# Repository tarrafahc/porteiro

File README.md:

porteiro
========

Repositório do porteiro do Tarrafa

O que é?
--------

O porteiro é o programa que roda no mula-sem-cabeça e serve principalmente para avisar quando tem ou não gente no Tarrafa. O porteiro centraliza várias funções. São elas: botão de presença, painel de LEDs, tomadas controladas por relé (pra ninguém esquecer a cafeteira ligada) e 'mood lamp'.

Estrutura dos arquivos
----------------------

A pasta 'arduino' tem o código que roda na plaquinha de arduino do porteiro. Este código atualiza o painel de LEDs com informação vinda pela serial, manda informação de alteração do estado do botão pela serial e controla a tomada e o 'mood lamp'.

A pasta 'eagle' tem os esquemáticos e o layout da plaquinha do shield de arduino do porteiro.

A pasta 'fonte' contém a fonte criada colaborativamente pelo Tarrafa para mostrar coisas no painel.

O script 'porteiro.py' roda no mula-sem-cabeça e fica mandando texto para o painel de LEDs e lendo informação do botão de presença.

Botão
-----

O botão deve ser pressionado pela primeira pessoa que entra no Tarrafa e pela última pessoa que sai do Tarrafa. Ao ligar, o botão manda uma mensagem para o mula-sem-cabeça para que ele atualize o status online do Tarrafa e acende a tomada controlada. Ao desligar, o botão manda novamente a mensagem para o mula-sem-cabeça e prepara a tomada para ser desligada.

Tomada controlada
-----------------

Na tomada controlada ficam ligadas (por enquanto) a luz externa do Tarrafa e a cafeteira. A tomada desliga um minuto depois de o botão ser desligado, dando tempo para que a luz externa ilumine a porta enquanto ela é fechada. A cafeteira também é desligada automaticamente para ninguém esquecer de desligá-la...

Painel de LEDs
--------------

O painel de LEDs foi reutilizado de alguma sucata. Durante encontros da N.E.R.D., foi feita a engenharia reversa do circuito eletrônico e foi feita uma interface para controlá-lo pelo Arduino. O painel tem 10 matrizes de 7x5 LEDs verdes/vermelhos. Dá pra passar qualquer coisa nos 10 caracteres do painel, mas no momento o que passa é a data, a hora e alguma mensagem de auto-ajuda qualquer...

Mood Lamp
---------

A 'mood lamp' fica ligada enquanto tem gente no Tarrafa. As cores da lâmpada ficam variando aleatoriamente num LED RGB.

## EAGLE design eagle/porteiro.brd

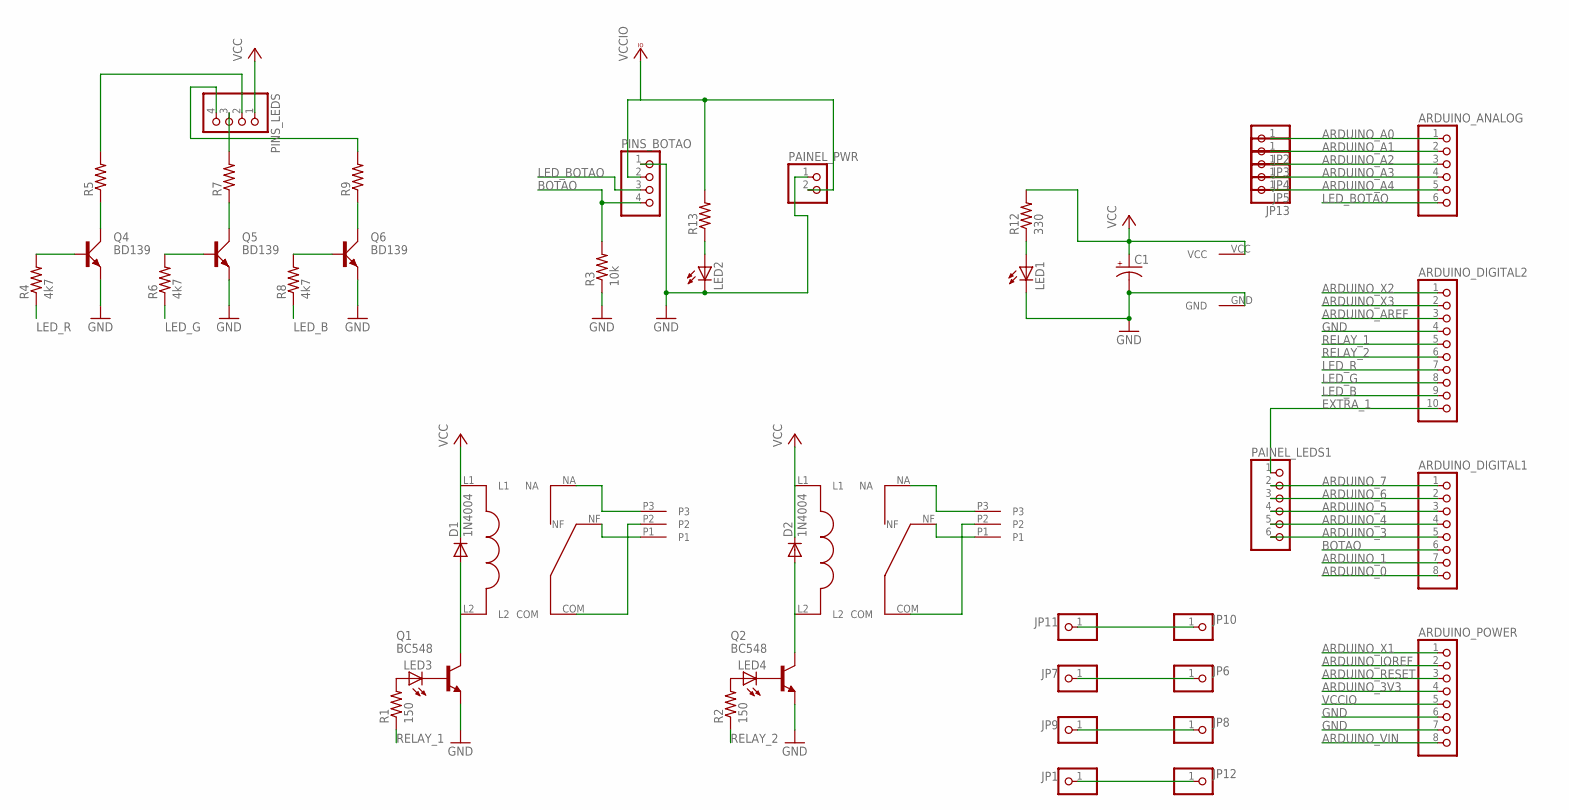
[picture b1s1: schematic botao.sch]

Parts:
ARDUINO_ANALOG: PINHD-1X6; 1X06
ARDUINO_DIGITAL1: PINHD-1X8; 1X08
ARDUINO_DIGITAL2: PINHD-1X10; 1X10
ARDUINO_POWER: PINHD-1X8; 1X08
C1: CPOL-USE5-10.5; E5-10,5
D1, D2: 1N4004; DO41-10
JP1, JP2, JP3, JP4, JP5, JP6, JP7, JP8, JP9, JP10, JP11, JP12, JP13: PINHD-1X1; 1X01
LED1, LED2, LED3, LED4: LED5MM
PAINEL_LEDS1: PINHD-1X6; 1X06
PAINEL_PWR: PINHD-1X2; 1X02
PINS_BOTAO: PINHD-1X4; 1X04
PINS_LEDS: PINHD-1X4; 1X04
Q1, Q2: BC548; TO92-EBC
Q4, Q5, Q6: BD139; TO126AV
R1, R2: 150; 0207/10
R3: 10k; 0207/7
R4, R6, R8: 4k7; 0207/10
R5, R7, R9: R-US_0411/15; 0411/15
R12: 330; 0207/10
R13: R-US_0207/7; 0207/7
U$1, U$3: RELAY
U$2, U$4: KRE3
U$7: DC

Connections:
ARDUINO_0: ARDUINO_DIGITAL1.8
ARDUINO_1: ARDUINO_DIGITAL1.7
ARDUINO_3: ARDUINO_DIGITAL1.5, PAINEL_LEDS1.6
ARDUINO_3V3: ARDUINO_POWER.4
ARDUINO_4: ARDUINO_DIGITAL1.4, PAINEL_LEDS1.5
ARDUINO_5: ARDUINO_DIGITAL1.3, PAINEL_LEDS1.4
ARDUINO_6: ARDUINO_DIGITAL1.2, PAINEL_LEDS1.3
ARDUINO_7: ARDUINO_DIGITAL1.1, PAINEL_LEDS1.2
ARDUINO_A0: ARDUINO_ANALOG.1, JP2.1
ARDUINO_A1: ARDUINO_ANALOG.2, JP3.1
ARDUINO_A2: ARDUINO_ANALOG.3, JP4.1
ARDUINO_A3: ARDUINO_ANALOG.4, JP5.1
ARDUINO_A4: ARDUINO_ANALOG.5, JP13.1
ARDUINO_AREF: ARDUINO_DIGITAL2.3
ARDUINO_IOREF: ARDUINO_POWER.2
ARDUINO_RESET: ARDUINO_POWER.3
ARDUINO_VIN: ARDUINO_POWER.8
ARDUINO_X1: ARDUINO_POWER.1
ARDUINO_X2: ARDUINO_DIGITAL2.1
ARDUINO_X3: ARDUINO_DIGITAL2.2
BOTAO: ARDUINO_DIGITAL1.6, PINS_BOTAO.4, R3.2
EXTRA_1: ARDUINO_DIGITAL2.10, PAINEL_LEDS1.1
GND: ARDUINO_DIGITAL2.4, ARDUINO_POWER.6, ARDUINO_POWER.7, C1.-, LED1.K (C), LED2.K (C), PAINEL_PWR.1, PINS_BOTAO.1, Q1.E, Q2.E, Q4.E, Q5.E, Q6.E, R3.1, U$7.GND
LED_B: ARDUINO_DIGITAL2.9, R8.1
LED_BOTAO: ARDUINO_ANALOG.6, PINS_BOTAO.3
LED_G: ARDUINO_DIGITAL2.8, R6.1
LED_R: ARDUINO_DIGITAL2.7, R4.1
unnamed: U$1.NF, U$2.P1
unnamed: D1.A, Q1.C, U$1.L2
unnamed: LED3.K (C), Q1.B
unnamed: U$1.NA, U$2.P3
unnamed: U$1.COM, U$2.P2
unnamed: D2.A, Q2.C, U$3.L2
unnamed: LED3.A, R1.2
unnamed: LED4.K (C), Q2.B
unnamed: U$3.NA, U$4.P3
unnamed: U$3.COM, U$4.P2
unnamed: JP1.1, JP12.1
unnamed: LED4.A, R2.2
unnamed: U$3.NF, U$4.P1
unnamed: Q4.B, R4.2
unnamed: Q4.C, R5.1
unnamed: PINS_LEDS.2, R5.2
unnamed: Q5.B, R6.2
unnamed: Q5.C, R7.1
unnamed: PINS_LEDS.3, R7.2
unnamed: Q6.B, R8.2
unnamed: Q6.C, R9.1
unnamed: PINS_LEDS.4, R9.2
unnamed: LED1.A, R12.1
unnamed: LED2.A, R13.1
RELAY_1: ARDUINO_DIGITAL2.5, R1.1
RELAY_2: ARDUINO_DIGITAL2.6, R2.1
VCC: C1.+, D1.C, D2.C, PINS_LEDS.1, R12.2, U$1.L1, U$3.L1, U$7.VCC
VCCIO: ARDUINO_POWER.5, PAINEL_PWR.2, PINS_BOTAO.2, R13.2
XTRA_1: JP10.1, JP11.1
XTRA_2: JP6.1, JP7.1
XTRA_3: JP8.1, JP9.1

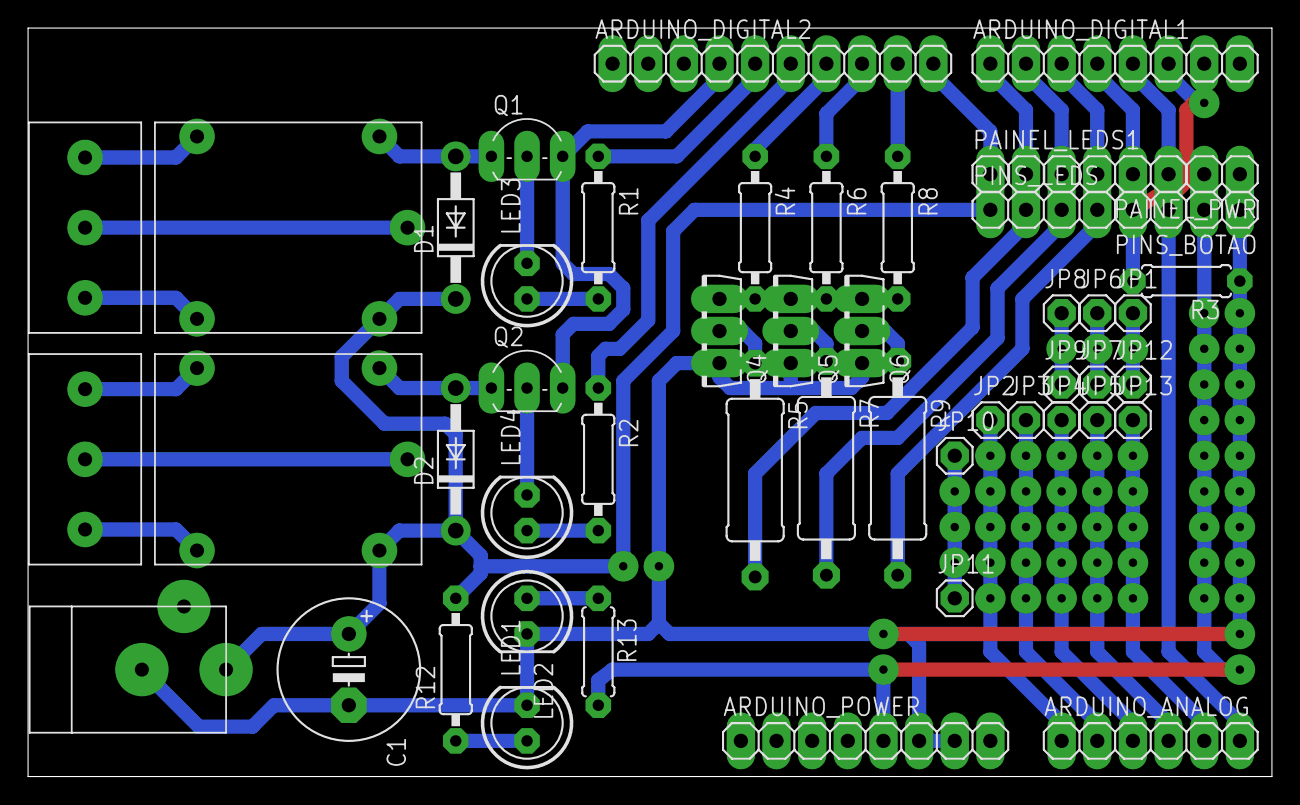
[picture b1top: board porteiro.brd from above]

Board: 2 copper layers, 88.6 x 53.3 mm, 49 parts (0 on the bottom side), 48 nets.

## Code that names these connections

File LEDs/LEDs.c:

#define F_CPU 16000000
#define BAUD  9600

#define MYUBRR (F_CPU/16/BAUD-1)

#include <avr/io.h>
#include <avr/interrupt.h>
#include <avr/pgmspace.h>
#include <avr/eeprom.h>

struct pino {
    volatile uint8_t *dir;
    volatile uint8_t *pin;
    volatile uint8_t *port;
    uint8_t bit;
};

static const struct pino _4015_d   = { &DDRB, &PINB, &PORTB, 0 }; /* marrom branco     */
static const struct pino _4015_clk = { &DDRD, &PIND, &PORTD, 7 }; /* verde  branco     */
static const struct pino _4015_mr  = { &DDRD, &PIND, &PORTD, 4 }; /* azul              */

static const struct pino _4094_clk = { &DDRD, &PIND, &PORTD, 6 }; /* marrom            */
static const struct pino _4094_str = { &DDRD, &PIND, &PORTD, 5 }; /* azul   branco     */
static const struct pino _4094_d   = { &DDRB, &PINB, &PORTB, 0 }; /* marrom branco [2] */
static const struct pino _4094_oe  = { &DDRD, &PIND, &PORTD, 3 }; /* verde             */

static const struct pino botao     = { &DDRD, &PIND, &PORTD, 2 }; /* botao             */
static const struct pino botao_led = { &DDRC, &PINC, &PORTC, 5 }; /* led do botao      */

static const struct pino rele_1    = { &DDRB, &PINB, &PORTB, 4 }; /* rele 1            */
static const struct pino rele_2    = { &DDRB, &PINB, &PORTB, 5 }; /* rele 2            */

static inline void set_output  (const struct pino *p) { *p->dir  |=  (1<<p->bit); }
static inline void set_input   (const struct pino *p) { *p->dir  &= ~(1<<p->bit); }
static inline void ligar_bit   (const struct pino *p) { *p->port |=  (1<<p->bit); }
static inline void desligar_bit(const struct pino *p) { *p->port &= ~(1<<p->bit); }
static inline uint8_t ler_bit  (const struct pino *p) { return *p->pin & (1<<p->bit); }
static inline void clk_d       (const struct pino *clk, const struct pino *d, uint8_t val)
{
    desligar_bit(clk);
    if (val) ligar_bit(d);
    else  desligar_bit(d);
    ligar_bit(clk);
}

static const struct pino pino_r = { &DDRB, &PINB, &PORTB, 1 }; /* led vermelho      */
static const struct pino pino_g = { &DDRB, &PINB, &PORTB, 3 }; /* led verde         */
static const struct pino pino_b = { &DDRB, &PINB, &PORTB, 2 }; /* led azul          */
static volatile uint8_t *led_r  = &OCR1AL;              /* led vermelho      */
static volatile uint8_t *led_g  = &OCR2A ;              /* led verde         */
static volatile uint8_t *led_b  = &OCR1BL;              /* led azul          */
static uint8_t cur_r = 0;
static uint8_t cur_g = 0;
static uint8_t cur_b = 0;

/* this is a cheap random number generator */
static uint8_t cheap_rand(void)
{
    static uint16_t state;
    state = state * 25173 + 13849;
    return state>>7;
}

extern PROGMEM uint8_t fonte[0x100][7];

static uint8_t out_buf[7][7] = {{0}}; /* [linha][50 bits] */
static uint8_t out_idx       =   0  ;

static void
print_char(uint8_t c, uint8_t pos)
{
    uint8_t letra[4] = { pgm_read_byte_near(&fonte[c][0]),
                         pgm_read_byte_near(&fonte[c][1]),
                         pgm_read_byte_near(&fonte[c][2]),
                         pgm_read_byte_near(&fonte[c][3]) };
    uint8_t linhas[7] = { letra[0] >> 4, letra[0] & 0x0F,
                          letra[1] >> 4, letra[1] & 0x0F,
                          letra[2] >> 4, letra[2] & 0x0F,
                          letra[3] >> 4 };
    uint8_t d[2] = { pos >> 3, (pos + 3) >> 3 };
    uint8_t q[2] = { pos  & 7, (8 - pos)  & 7 };
    uint8_t mask[2] = { 0xff & ~(0x0f << q[0]), 0xff << (q[0]-4) };

    for (uint8_t i = 0; i < 7; i++) {
        out_buf[i][d[0]] = (out_buf[i][d[0]] & mask[0]) | (linhas[i] << q[0]);
        if (d[0] != d[1])
            out_buf[i][d[1]] = (out_buf[i][d[1]] & mask[1]) | (linhas[i] >> q[1]);
    }
}

static void
init_button()
{
    EICRA = (1 << ISC01); /* falling edge */
    EIMSK = (1 << INT0);
}

static void
init_serial()
{
    UBRR0H = MYUBRR >> 8;
    UBRR0L = MYUBRR;
    UCSR0C = (1 << UCSZ00) | (1 << UCSZ01); /* 8-bit */
    /* enable rx, tx, and USART_RX interrupt */
    UCSR0B = (1 << RXEN0 ) | (1 << TXEN0 ) | (1 << RXCIE0);
}

static void
init_timer()
{
    /* timer0 = main timer */
    TCCR0A = 0;                         /* normal port operation */
    TCCR0B = (1 << CS01) | (1 << CS00); /* prescaler = 64 */
    TIFR0  = (1 << TOV0);               /* clear pending interrupts */
    TIMSK0 = (1 << TOIE0);              /* enable TIMER0_OVF interrupt */
}

static void
init_pwm()
{
    /* pwm on arduino pins 9 and 10 */
    /* phase-correct pwm, 8-bit, OC1A and OC1B */
    TCCR1A = (1 << WGM10) | (1 << COM1A1) | (1 << COM1B1);
    TCCR1B = (1 << CS10); /* prescaler = 1 */

    /* pwm on arduino pin 11 */
    /* phase-correct pwm, 8-bit, OC2A */
    TCCR2A = (1 << WGM20) | (1 << COM2A1);
    TCCR2B = (1 << CS20); /* prescaler = 1 */
}

static void loop()
{
}

static uint8_t status = 0;

void main(void) __attribute__((noreturn));
void main()
{
    init_button();
    init_serial();
    init_timer();
    init_pwm();
    sei();  /* enable interrupts */

    set_output(&_4015_d  );
    set_output(&_4015_clk);
    set_output(&_4015_mr );
    set_output(&_4094_clk);
    set_output(&_4094_str);
    set_output(&_4094_d  );
    set_output(&_4094_oe );

    set_output(&pino_r);
    set_output(&pino_g);
    set_output(&pino_b);

    set_input (&botao    );
    set_output(&botao_led);

    set_output(&rele_1);
    set_output(&rele_2);

    desligar_bit(&_4015_mr);
    ligar_bit(&_4094_oe);
    while (1)
        loop();
}

static uint8_t red   = 1;
static uint8_t green = 0;

static uint16_t turnoff_count = 0;
static uint8_t debounce_count = 0;

/* main timer interrupt: F_CPU / (256 * 64) = 976.5625 Hz, 1.024 ms */
ISR(TIMER0_OVF_vect)
{
    if (debounce_count) {
        debounce_count--;
        if (!debounce_count && ler_bit(&botao)) {
            /* 51.2 ms debounce */
            status = !status;
            if (!status) {
                desligar_bit(&botao_led);
                *led_r = 255;
                *led_g = 255;
                *led_b = 255;
                turnoff_count = 0xffff;
            } else {
                ligar_bit(&botao_led);
                ligar_bit(&rele_1);
                ligar_bit(&rele_2);
            }
            UDR0 = status + '0';
        }
    }

    if (!status) {
        if (turnoff_count) {
            turnoff_count--;
            if (!turnoff_count) {
                /* 67.10784s delay */
                desligar_bit(&rele_1);
                desligar_bit(&rele_2);
                *led_r = 0;
                *led_g = 0;
                *led_b = 0;
            }
        }
        return;
    }

    static uint8_t led_count = 0;

    if (++led_count == 10) {
        uint8_t old_r = *led_r;
        uint8_t old_g = *led_g;
        uint8_t old_b = *led_b;
        if (old_r == cur_r && old_g == cur_g && old_b == cur_b) {
            cur_r = cheap_rand();
            cur_g = cheap_rand();
            cur_b = cheap_rand();
        }
        if (old_r > cur_r) *led_r -= 1; else if (old_r < cur_r) *led_r += 1;
        if (old_g > cur_g) *led_g -= 1; else if (old_g < cur_g) *led_g += 1;
        if (old_b > cur_b) *led_b -= 1; else if (old_b < cur_b) *led_b += 1;
        led_count = 0;
    }

    static uint8_t i = 0;
    desligar_bit(&_4094_str);
    for (uint8_t j = 0; j < 50; j++)
        clk_d(&_4094_clk, &_4094_d, ((out_buf[i][j>>3]>>(j&7))&1));
    desligar_bit(&_4094_oe);
    ligar_bit(&_4094_str);
    for (uint8_t j = 0; j < 7; j++) {
        clk_d(&_4015_clk, &_4015_d, (j==i)&red  );
        clk_d(&_4015_clk, &_4015_d, (j==i)&green);
    }
    clk_d(&_4015_clk, &_4015_d, 0);
    ligar_bit(&_4094_oe);
    if (++i == 7)
        i = 0;
}

/* usart rx interrupt */
ISR(USART_RX_vect)
{
    print_char(UDR0, out_idx++ * 5);
    if (out_idx == 10)
        out_idx = 0;
}

/* button interrupt */
ISR(INT0_vect)
{
    debounce_count = 50;
}

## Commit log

2013-09-18 commit inicial
2013-09-18 fonte: mais letras
2013-10-07 arduino: remover Serial.println() de depuração
2013-10-07 arduino: reduzir loops
2013-10-09 arduino: usar index para buffer de texto
2013-10-09 programa: largar arduino, escrever direto em C
2013-10-09 programa: cosméticos
2013-12-06 programa: expandir seleção de bits em DDRC
2013-12-06 programa: ajustar pinos para placa nova
    - Configurar pinos individualmente;
    - Usar funções inline no lugar de macros;
    - Atualizar numero dos pinos e suas portas.
2013-12-06 programa: tornar loop uma função estática
2013-12-06 programa: remover buffer de texto
2013-12-06 programa: documentar frequencia do main timer
2013-12-07 programa: adicionar 'mood lamp'
2013-12-07 programa: adicionar botao
2013-12-07 programa: reorganizar, renomear, documentar...
2013-12-07 Makefile: mudar gravador para Arduino Duemilanove
2013-12-07 eagle: adicionar
2013-12-07 fonte: adicionar target clean
2013-12-07 renomear LEDs para arduino
2013-12-07 painel: usar ttyUSB0
2013-12-07 script: mover arquivo para o root
2013-12-16 programa: gravar status na EEPROM
2013-12-16 programa: dormir no loop
2013-12-16 script: remover temperatura
2013-12-16 script: esperar reset do arduino
2013-12-16 script: ler botao, usando timeout como sleep
2014-01-05 painel: documentar código
2014-01-05 painel: esperar 2 segundos para dar tempo ao arduino
2014-01-05 renomear painel para porteiro
2014-01-05 renomear LEDs para porteiro
2014-01-05 eagle: renomear botao para porteiro
2014-01-05 adicionar README.md genérico
2017-09-24 adicionadas as funções de tweet e de mudança da imagem no botaobiarra
2017-09-28 deletado um botao() a mais
